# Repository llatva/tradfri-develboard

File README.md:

# tradfri-develboard

Based on work by basilfx@github, see: https://github.com/basilfx/TRADFRI-Hacking

**LICENSE**

Creative Commons BY Attribution 4.0 International

**DISCLAIMER**

This repository is provided "AS IS", without warranty of any kind, express or implied.
This content is not affiliated with IKEA of Sweden AB. Use the information on your own risk.

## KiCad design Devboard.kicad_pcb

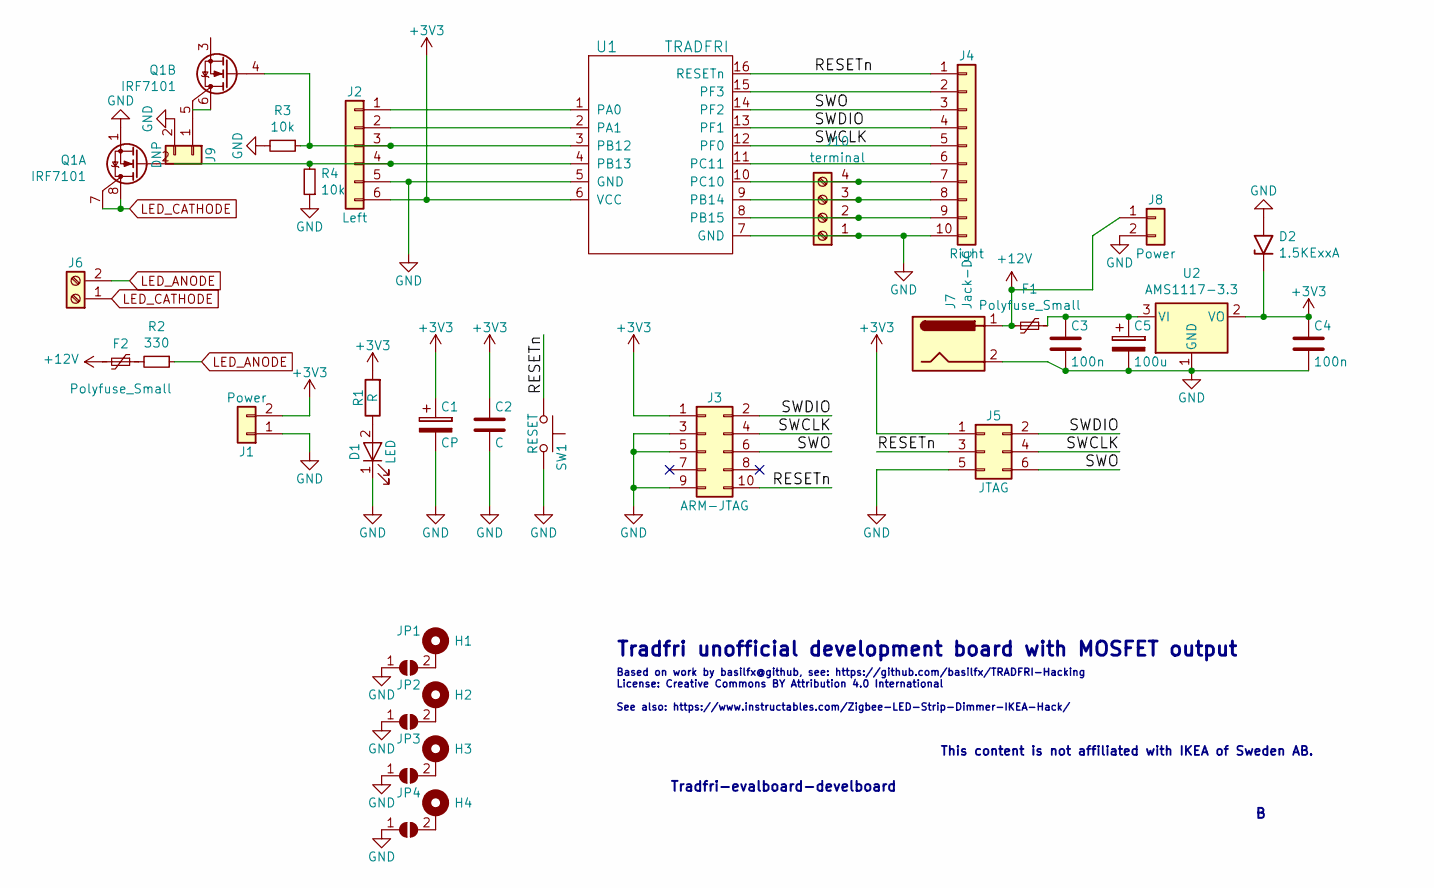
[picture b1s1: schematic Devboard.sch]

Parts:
C1: CP; CP_Elec_5x5.4
C2: C; C_0805_2012Metric_Pad1.18x1.45mm_HandSolder
C3, C4: 100n; C_0805_2012Metric_Pad1.18x1.45mm_HandSolder
C5: 100u; CP_Elec_5x5.4
D1: LED; LED_0805_HandSoldering
D2: 1.5KExxA; D_SMB_Handsoldering
F1, F2: Polyfuse_Small; R_Axial_DIN0207_L6.3mm_D2.5mm_P10.16mm_Horizontal
H1, H2, H3, H4: MountingHole_Pad; MountingHole_3.5mm_Pad_TopBottom
J1: Power; Pin_Header_Straight_1x02_Pitch2.54mm
J2: Left; Pin_Header_Straight_1x06_Pitch2.54mm
J3: ARM-JTAG; Pin_Header_Straight_2x05_Pitch1.27mm
J4: Right; Pin_Header_Straight_1x10_Pitch2.54mm
J5: JTAG; Pin_Header_Straight_2x03_Pitch2.54mm
J6: Screw_Terminal_01x02; TerminalBlock_Phoenix_MKDS-1,5-2_1x02_P5.00mm_Horizontal
J7: Jack-DC; BarrelJack_Horizontal
J8: Power; PinHeader_1x02_P2.54mm_Vertical
J9: DNP; PinHeader_1x02_P2.54mm_Vertical
J10: terminal; TerminalBlock_Phoenix_MKDS-1,5-4_1x04_P5.00mm_Horizontal
JP1, JP2, JP3, JP4: SolderJumper_2_Open; SolderJumper-2_P1.3mm_Open_RoundedPad1.0x1.5mm
Q1: IRF7101; SO-8_3.9x4.9mm_P1.27mm
R1: R; R_0805_HandSoldering
R2: 330; R_1206_3216Metric_Pad1.30x1.75mm_HandSolder
R3, R4: 10k; R_1206_3216Metric_Pad1.30x1.75mm_HandSolder
SW1: RESET; SW_PUSH_6mm
U1: TRADFRI; TRADFRI_PCB2.0
U2: AMS1117-3.3; SOT-223-3_TabPin2

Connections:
+3V3: C1.1, C2.1, C4.1, D2.1 (A1), J1.2, J2.6, J3.1, J5.1, R1.2, U1.6 (VCC), U2.2 (VO)
+12V: F1.2, F2.2, J7.1, J8.1
/RESETn: J3.10, J4.1, J5.3, SW1.1, U1.16 (RESETn)
/SWCLK: J3.4, J4.5, J5.4, U1.12 (PF0)
/SWDIO: J3.2, J4.4, J5.2, U1.13 (PF1)
/SWO: J3.6, J4.3, J5.6, U1.14 (PF2)
GND: C1.2, C2.2, C3.2, C4.2, C5.2, D1.1 (K), D2.2 (A2), J1.1, J2.5, J3.3, J3.5, J3.9, J4.10, J5.5, J7.2, J8.2, J9.2, J10.1, JP1.1 (A), JP2.1 (A), JP3.1 (A), JP4.1 (A), Q1.1 (S2), R3.2, R4.1, SW1.2, U1.5 (GND), U1.7 (GND), U2.1 (GND)
LED_ANODE: J6.2, R2.1
LED_CATHODE: J6.1, Q1.7 (D2), Q1.8 (D2)
unnamed: C3.1, C5.1, F1.1, U2.3 (VI)
unnamed: D1.2 (A), R1.1
unnamed: F2.1, R2.2
unnamed: H1.1, JP1.2 (B)
unnamed: H2.1, JP2.2 (B)
unnamed: H3.1, JP3.2 (B)
unnamed: H4.1, JP4.2 (B)
unnamed: J2.1, U1.1 (PA0)
unnamed: J2.2, U1.2 (PA1)
unnamed: J2.3, Q1.4 (G2), R3.1, U1.3 (PB12)
unnamed: J2.4, Q1.2 (G1), R4.2, U1.4 (PB13)
unnamed: J4.2, U1.15 (PF3)
unnamed: J4.6, U1.11 (PC11)
unnamed: J9.1, Q1.5 (D2)
unnamed: J4.9, J10.2, U1.8 (PB15)
unnamed: J4.8, J10.3, U1.9 (PB14)
unnamed: J4.7, J10.4, U1.10 (PC10)

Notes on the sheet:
Based on work by basilfx@github, see: https://github.com/basilfx/TRADFRI-Hacking License: Creative Commons BY Attribution 4.0 International See also: https://www.instructables.com/Zigbee-LED-Strip-Dimmer-IKEA-Hack/
Tradfri unofficial development board with MOSFET output
Tradfri-evalboard-develboard
This content is not affiliated with IKEA of Sweden AB.

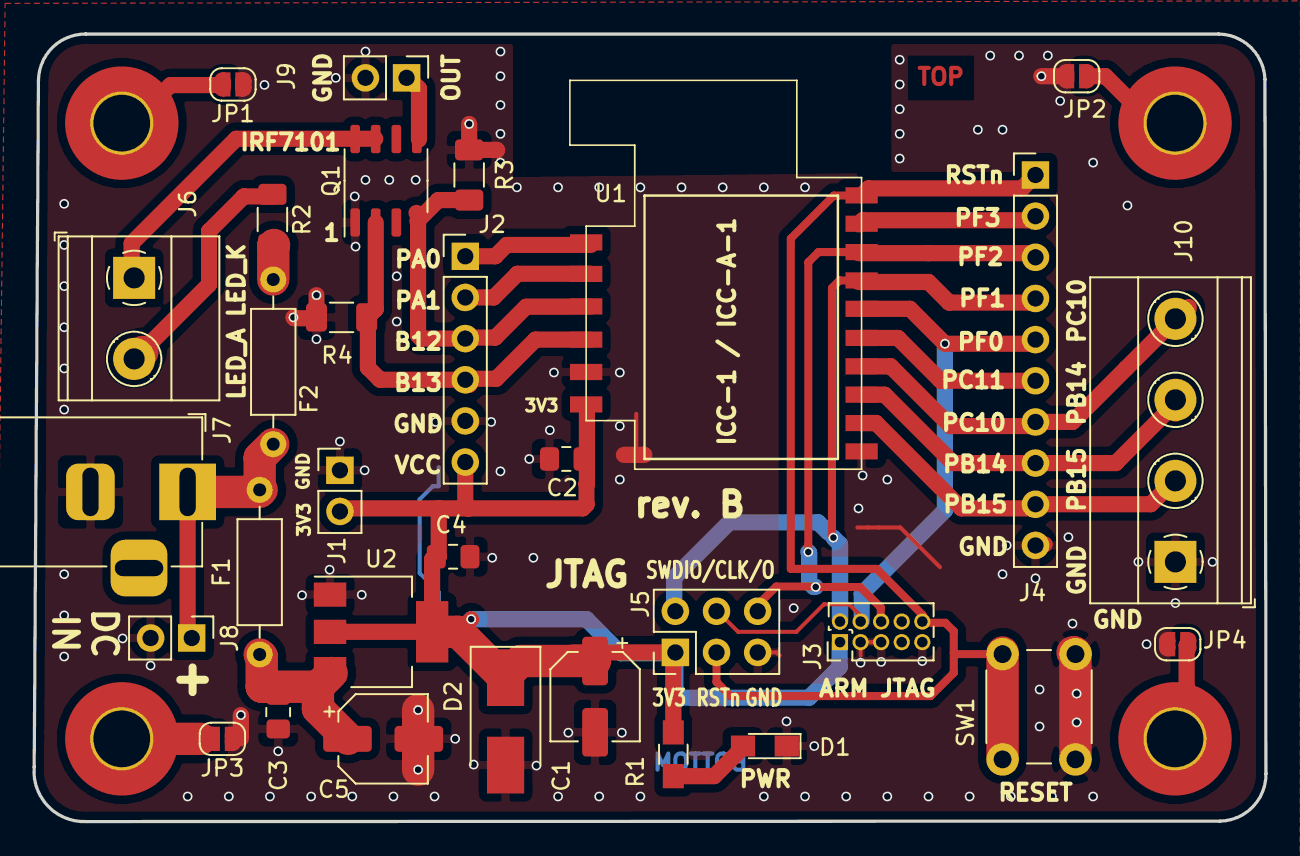
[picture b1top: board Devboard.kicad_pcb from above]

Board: 2 copper layers, 76.0 x 48.6 mm, 35 parts (0 on the bottom side), 26 nets.

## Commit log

2021-11-19 revision A to github
2021-11-19 schematic texts and minor stylishing
2021-11-19 schamatic printout
2021-11-19 enhancements to pcb, this will be possible rev B
2022-01-28 remove old files
2022-02-21 rev B 3D images
2022-02-22 remove old gerbers
